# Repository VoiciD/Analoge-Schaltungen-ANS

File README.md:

# Biquad-Filter: Analoge Signalverarbeitung im digitalen Zeitalter

Auch in einer zunehmend digitalen Welt spielt analoge Schaltungstechnik eine zentrale Rolle – insbesondere in der Signalverarbeitung. Physikalische Signale, wie elektromagnetische Wellen bei Funkstrecken, liegen zunächst in analoger Form vor und werden erst später digital verarbeitet. Vor der Digitalisierung durch einen ADC ist daher eine analoge Vorverarbeitung unerlässlich. Sie verbessert den Signal-zu-Rausch-Abstand (SNR) und schützt vor Informationsverlusten.

Ein wichtiger Bestandteil dieser analogen Vorverarbeitung ist die Signalfilterung. Nur durch gezielte Unterdrückung von Rauschen und Störfrequenzen können digitale Systeme das Nutzsignal später korrekt verarbeiten. Die Einhaltung des Nyquist-Kriteriums ist dabei essenziell.

Zentrales Thema dieses Moduls ist der sogenannte **Biquad-Filter** – ein universeller, analoger Filter zweiter Ordnung. Er lässt sich einfach mit wenigen Operationsverstärkern (OPs) realisieren und bietet vielfältige Einsatzmöglichkeiten. Unterschiedliche Kombinationen liefern Hochpass-, Bandpass- oder Tiefpassfunktionen. Für komplexere Filter werden mehrere Biquad-Stufen kaskadiert.

## Zielsetzung

Ziel ist es, den Aufbau und das Verhalten eines analogen Biquad-Filters zu verstehen sowie seine Übertragungsfunktion theoretisch herzuleiten. Besondere Aufmerksamkeit gilt dabei dem **Gütefaktor** \\( Q \\) und dem **Verstärkungsfaktor** \\( H_0 \\).

Nach der theoretischen Betrachtung folgt die praktische Umsetzung auf dem **ASLK-PRO Board**, um Erfahrungen mit den Bauteilwerten (Widerstände, Kondensatoren etc.) zu sammeln. Anschließend wird auf Basis dieser Erkenntnisse eine eigene **Leiterplatte (PCB)** entwickelt.

> **Hinweis:**  
> Der Bericht wurde bewusst in **LaTeX** anstelle von *Quarto* erstellt, da sowohl das **Blockschaltbild (BSB)** als auch die **Schaltpläne** in LaTeX umgesetzt wurden und sich dadurch eine einheitliche Darstellung mit präziser Kontrolle über Formeln und Layout ergab. Falls doch noch Änderung erfolgen und ein Bericht in Quarto erstellt wird, ist dieser unter https://voicid.github.io/Analoge-Schaltungen-ANS/ zu finden.

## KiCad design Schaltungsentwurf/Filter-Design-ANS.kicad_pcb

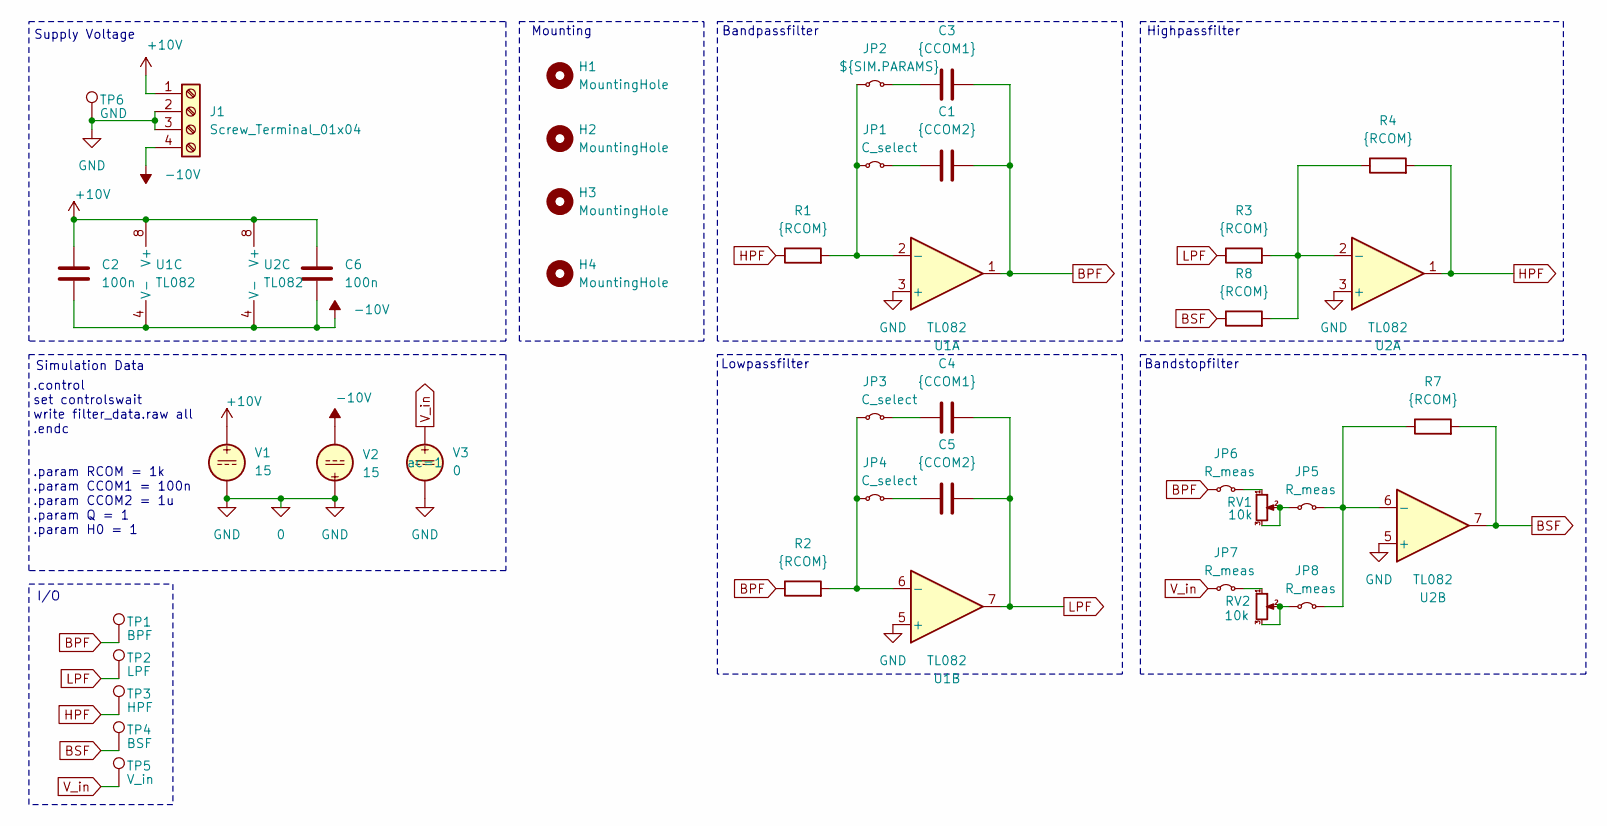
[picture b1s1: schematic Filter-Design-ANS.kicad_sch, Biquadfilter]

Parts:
C1, C5: {CCOM2}; C_Rect_L7.0mm_W2.5mm_P5.00mm
C2, C6: 100n; C_Disc_D3.0mm_W2.0mm_P2.50mm
C3, C4: {CCOM1}; C_Rect_L7.0mm_W2.5mm_P5.00mm
H1, H2, H3, H4: MountingHole; MountingHole_2.2mm_M2_DIN965
J1: Screw_Terminal_01x04; TerminalBlock_Altech_AK300-4_P5.00mm
JP1, JP3, JP4: C_select; PinHeader_1x02_P2.54mm_Vertical
JP2: ${SIM.PARAMS}; PinHeader_1x02_P2.54mm_Vertical
JP5, JP6, JP7, JP8: R_meas; PinHeader_1x02_P2.54mm_Vertical
R1, R2, R3, R4, R7, R8: {RCOM}; R_Axial_DIN0204_L3.6mm_D1.6mm_P7.62mm_Horizontal
RV1, RV2: 10k; Potentiometer_Bourns_3266W_Vertical
TP1: BPF; TestPoint_Loop_D1.80mm_Drill1.0mm_Beaded; Mouser Part Number 534-5015
TP2: LPF; TestPoint_Loop_D1.80mm_Drill1.0mm_Beaded; Mouser Part Number 534-5015
TP3: HPF; TestPoint_Loop_D1.80mm_Drill1.0mm_Beaded; Mouser Part Number 534-5015
TP4: BSF; TestPoint_Loop_D1.80mm_Drill1.0mm_Beaded; Mouser Part Number 534-5015
TP5: V_in; TestPoint_Loop_D1.80mm_Drill1.0mm_Beaded; Mouser Part Number 534-5015
TP6: GND; TestPoint_Loop_D1.80mm_Drill1.0mm_Beaded; Mouser Part Number 534-5015
U1, U2: TL082; DIP-8_W10.16mm
V1, V2: 15
V3: 0

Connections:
0: J1.2, J1.3, TP6.1, U1.3 (+), U1.5 (+), U2.3 (+), U2.5 (+), V1.2, V2.1, V3.2
+10V: C2.1, C6.1, J1.1, U1.8 (V+), U2.8 (V+), V1.1
-10V: C2.2, C6.2, J1.4, U1.4 (V-), U2.4 (V-), V2.2
BPF: C1.2, C3.2, JP6.1 (A), R2.1, TP1.1, U1.1
BSF: R7.2, R8.1, TP4.1, U2.7
HPF: R1.1, R4.2, TP3.1, U2.1
LPF: C4.2, C5.2, R3.1, TP2.1, U1.7
unnamed: JP1.1 (A), JP2.1 (A), R1.2, U1.2 (-)
unnamed: C1.1, JP1.2 (B)
unnamed: C3.1, JP2.2 (B)
unnamed: JP3.1 (A), JP4.1 (A), R2.2, U1.6 (-)
unnamed: C4.1, JP3.2 (B)
unnamed: C5.1, JP4.2 (B)
unnamed: JP5.1 (A), RV1.2, RV1.3
unnamed: JP5.2 (B), JP8.2 (B), R7.1, U2.6 (-)
unnamed: JP6.2 (B), RV1.1
unnamed: JP7.2 (B), RV2.1
unnamed: JP8.1 (A), RV2.2, RV2.3
unnamed: R3.2, R4.1, R8.2, U2.2 (-)
V_in: JP7.1 (A), TP5.1, V3.1

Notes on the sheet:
Simulation Data
Supply Voltage
I/O
Bandstopfilter
Lowpassfilter
.control set controlswait write filter_data.raw all .endc
.param RCOM = 1k .param CCOM1 = 100n .param CCOM2 = 1u .param Q = 1 .param H0 = 1
Bandpassfilter
Mounting
Highpassfilter

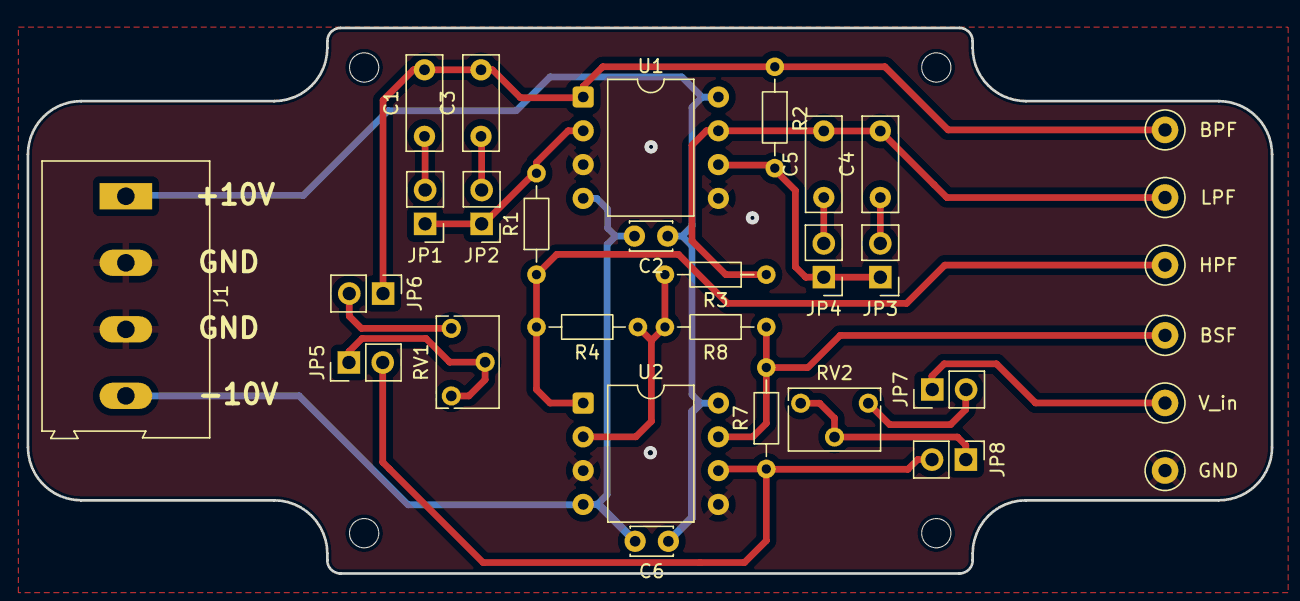
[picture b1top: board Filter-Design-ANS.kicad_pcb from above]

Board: 4 copper layers, 93.5 x 41.0 mm, 35 parts (0 on the bottom side), 20 nets.

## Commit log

2025-07-01 Update LICENSE
